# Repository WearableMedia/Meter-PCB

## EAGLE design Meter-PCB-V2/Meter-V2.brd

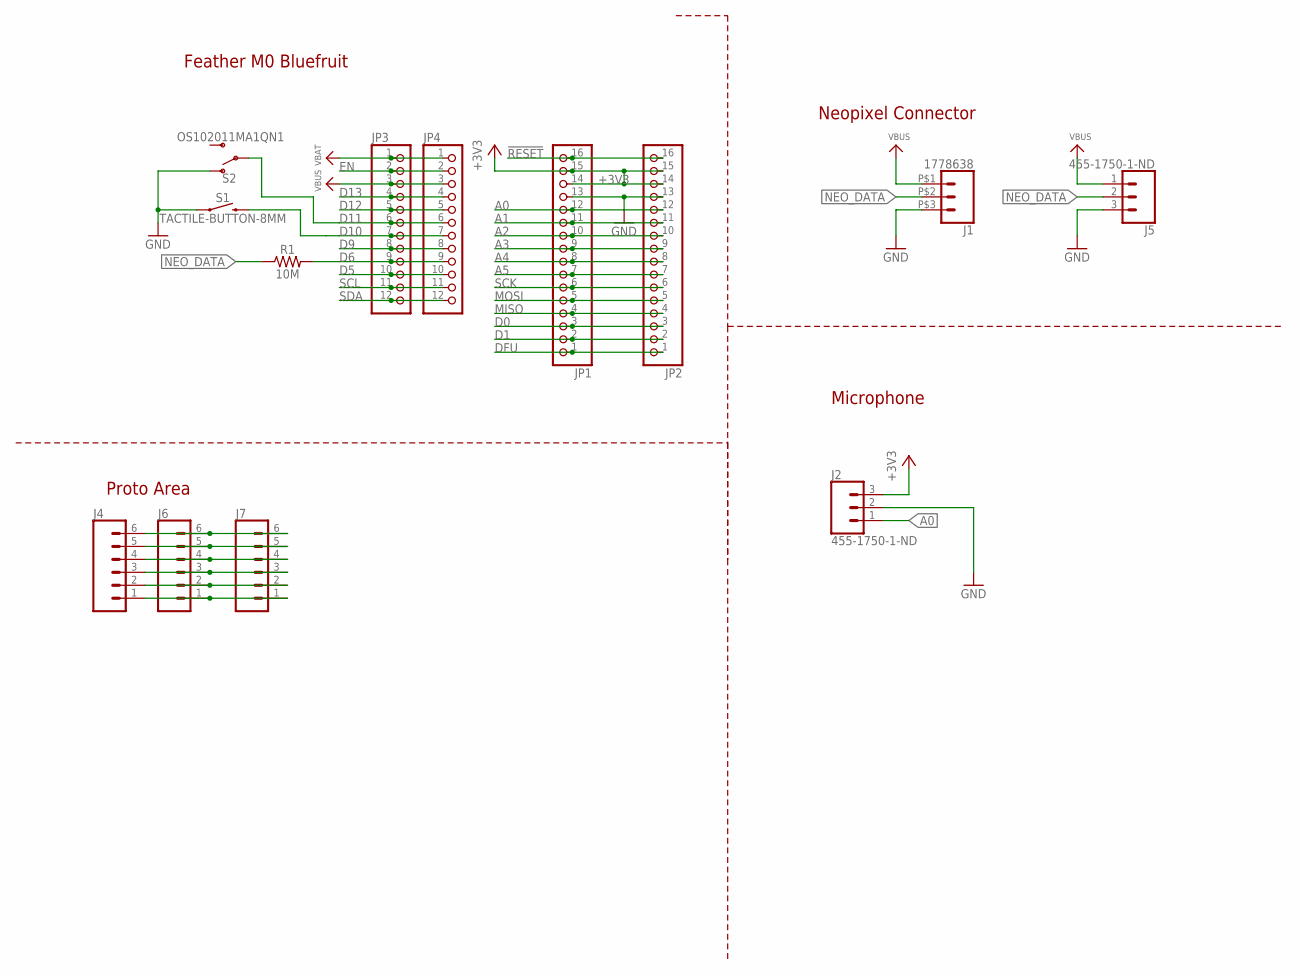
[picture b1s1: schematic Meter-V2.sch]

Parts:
J1: 1778638
J2, J5: 455-1750-1-ND; 1X03
J4, J6, J7: CONN_06NO_SILK_NO_POP; 1X06_NO_SILK
JP1, JP2: HEADER-1X16ROUND; 1X16_ROUND
JP3, JP4: HEADER-1X12; 1X12_ROUND
R1: 10M; AXIAL-0.3
S1: TACTILE-BUTTON-8MM; BUTTON-8MM
S2: OS102011MA1QN1

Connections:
!RESET: JP1.16, JP2.16
+3V3: J2.3, JP1.14, JP1.15, JP2.14, JP2.15
A0: J2.1, JP1.12, JP2.12
A1: JP1.11, JP2.11
A2: JP1.10, JP2.10
A3: JP1.9, JP2.9
A4: JP1.8, JP2.8
A5: JP1.7, JP2.7
D0: JP1.3, JP2.3
D1: JP1.2, JP2.2
D5: JP3.10, JP4.10
D6: JP3.9, JP4.9, R1.P$2 (2)
D9: JP3.8, JP4.8
D10: JP3.7, JP4.7, S1.P$2 (2), S1.P$3 (2)
D11: JP3.6, JP4.6, S2.P$2
D12: JP3.5, JP4.5
D13: JP3.4, JP4.4
DFU: JP1.1, JP2.1
EN: JP3.2, JP4.2
GND: J1.P$3 (3), J2.2, J5.3, JP1.13, JP2.13, S1.P$1 (1), S1.P$4 (1), S2.P$1 (O)
MISO: JP1.4, JP2.4
MOSI: JP1.5, JP2.5
unnamed: J4.6, J6.6, J7.6
unnamed: J4.5, J6.5, J7.5
unnamed: J4.4, J6.4, J7.4
unnamed: J4.3, J6.3, J7.3
unnamed: J4.2, J6.2, J7.2
unnamed: J4.1, J6.1, J7.1
NEO_DATA: J1.P$2 (2), J5.2, R1.P$1 (1)
SCK: JP1.6, JP2.6
SCL: JP3.11, JP4.11
SDA: JP3.12, JP4.12
VBAT: JP3.1, JP4.1
VBUS: J1.P$1 (1), J5.1, JP3.3, JP4.3

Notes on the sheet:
Feather M0 Bluefruit
Proto Area
Neopixel Connector
Microphone

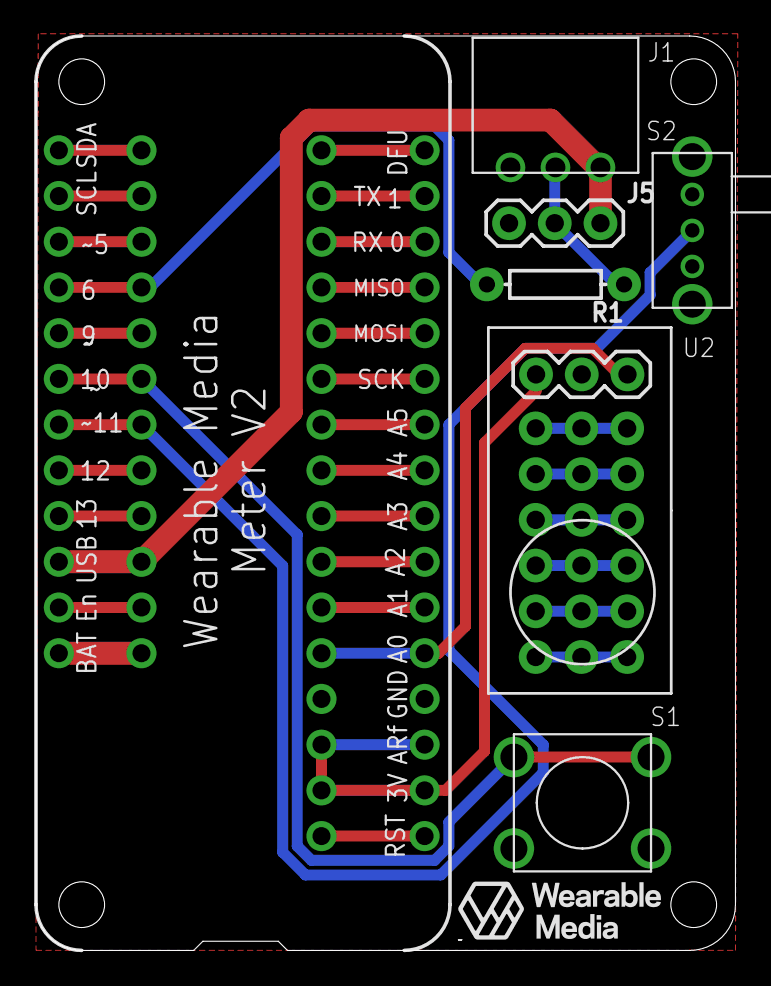
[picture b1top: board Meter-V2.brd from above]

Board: 2 copper layers, 38.9 x 50.8 mm, 15 parts (1 on the bottom side), 34 nets.

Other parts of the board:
U$3, U$4: WM_LOGO_MINI

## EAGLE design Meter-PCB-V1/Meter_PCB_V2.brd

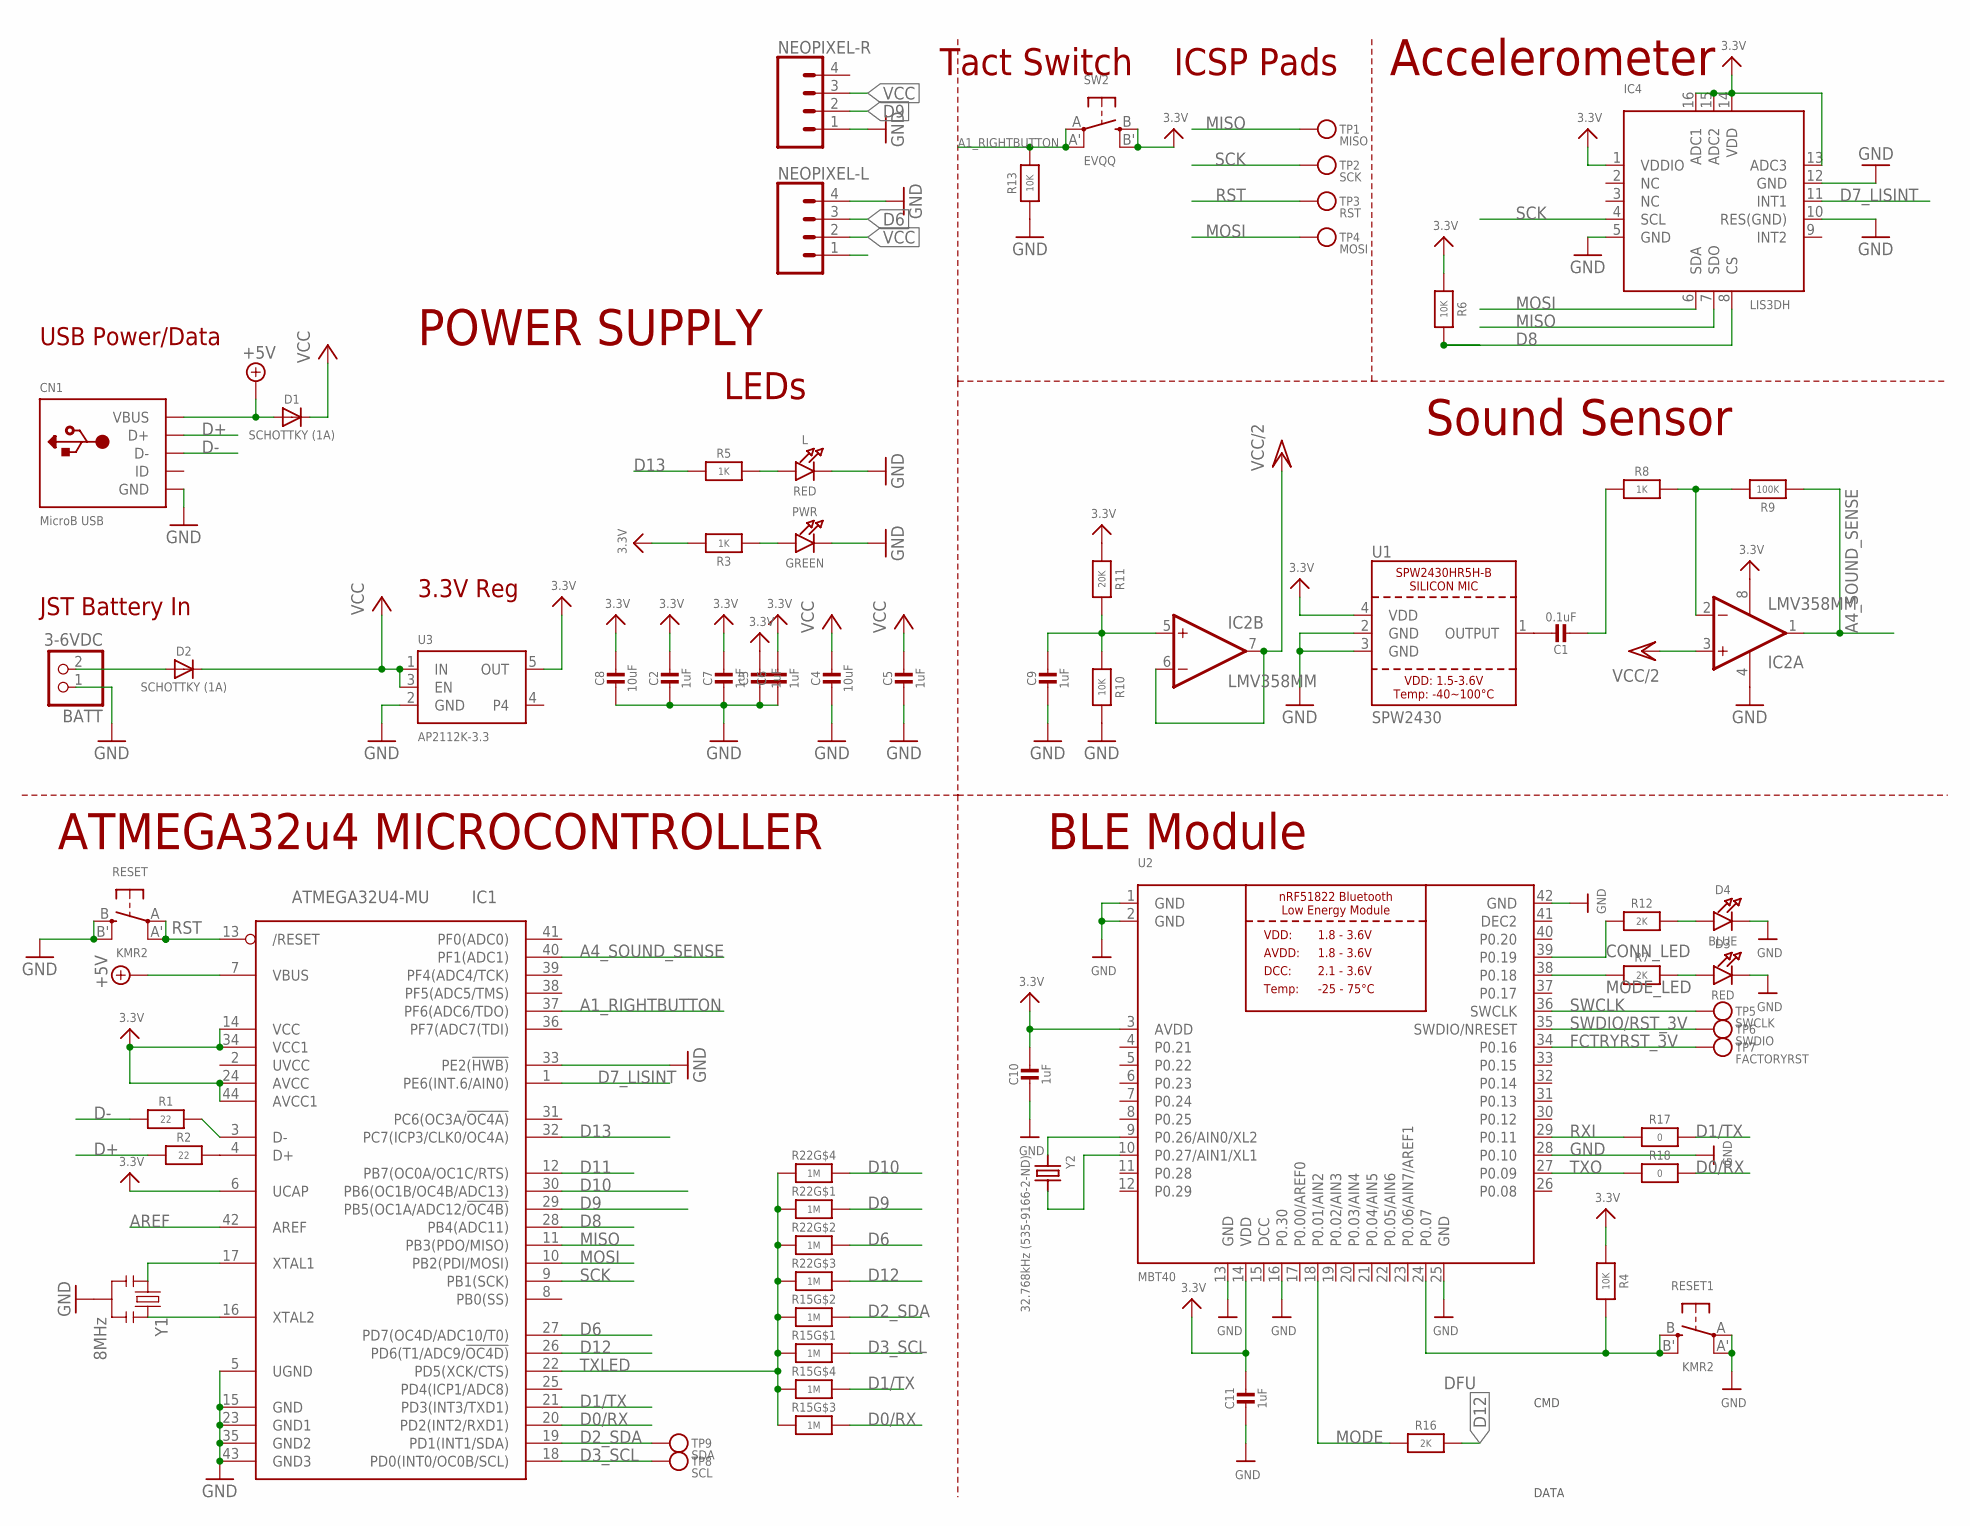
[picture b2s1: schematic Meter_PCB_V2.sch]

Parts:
BATT: 3-6VDC; JSTPH2
C1: 0.1uF; 0603-NO
C2, C3, C5, C6, C7, C9: 1uF; 0603-NO
C4, C8: 10uF; 0805-NO
C10, C11: 1uF; 0805-NO
CN1: MicroB USB; 4UCONN_20329_V2
D1, D2: SCHOTTKY (1A); SOD-123
D3: RED; CHIPLED_0805_NOOUTLINE
D4: BLUE; CHIPLED_0805_NOOUTLINE
IC1: ATMEGA32U4-MU; TQFN44_7MM
IC2: LMV358MM; MSOP08
IC4: LIS3DH; LGA16_3X3MM
L: RED; CHIPLED_0805_NOOUTLINE
NEOPIXEL-L: CONN_04; 1X04
NEOPIXEL-R: CONN_04; 1X04
PWR: GREEN; CHIPLED_0805_NOOUTLINE
R1, R2: 22; 0603-NO
R3, R5, R8: 1K; 0603-NO
R4: 10K; 0805-NO
R6, R10, R13: 10K; 0603-NO
R7, R12, R16: 2K; 0805-NO
R9: 100K; 0603-NO
R11: 20K; 0603-NO
R15, R22: 1M; RESPACK_4X0603_NO
R17, R18: 0; 0603-NO
RESET, RESET1: KMR2; BTN_KMR2_4.6X2.8
SW2: EVQQ; EVQ-Q2_SMALLER
TP1: MISO; TESTPOINT_ROUND_1.5MM
TP2: SCK; TESTPOINT_ROUND_1.5MM
TP3: RST; TESTPOINT_ROUND_1.5MM
TP4: MOSI; TESTPOINT_ROUND_1.5MM
TP5: SWCLK; TESTPOINT_ROUND_1.5MM
TP6: SWDIO; TESTPOINT_ROUND_1.5MM
TP7: FACTORYRST; TESTPOINT_ROUND_1.5MM
TP8: SCL; TESTPOINT_ROUND_1.5MM
TP9: SDA; TESTPOINT_ROUND_1.5MM
U1: SPW2430; SPW2430HR5H-B
U2: MBT40; BLE_MODULE_RAYTAC_MDBT40
U3: AP2112K-3.3; SOT23-5
Y1: 8MHz; RESONATOR-SMD
Y2: 32.768kHz (535-9166-2-ND); CRYSTAL_CYL_2X6MM_SMT

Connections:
3.3V: C2.1, C3.1, C6.1, C7.1, C8.1, C10.1, C11.1, IC1.6 (UCAP), IC1.14 (VCC), IC1.24 (AVCC), IC1.34 (VCC1), IC1.44 (AVCC1), IC2.8 (V+), IC4.1 (VDDIO), IC4.13 (ADC3), IC4.14 (VDD), IC4.15 (ADC2), IC4.16 (ADC1), NEOPIXEL-L.1, R3.2, R4.1, R6.1, R11.1, SW2.B (S), SW2.B' (S1), U1.4 (VDD), U2.3 (AVDD), U2.14 (VDD), U3.5 (OUT)
+5V: CN1.VBUS, D1.A, IC1.7 (VBUS)
A1_RIGHTBUTTON: IC1.37 (PF6(ADC6/TDO)), R13.2, SW2.A, SW2.A' (P1)
A4_SOUND_SENSE: IC1.40 (PF1(ADC1)), IC2.1 (OUT), R9.1
AREF: IC1.42 (AREF)
CONN_LED: R12.1, U2.39 (P0.19)
D0/RX: IC1.20 (PD2(INT2/RXD1)), R15.6 (2), R18.2
D1/TX: IC1.21 (PD3(INT3/TXD1)), R15.5 (2), R17.2
D2_SDA: IC1.19 (PD1(INT1/SDA)), R15.7 (2), TP9.P$1
D3_SCL: IC1.18 (PD0(INT0/OC0B/SCL)), R15.8 (2), TP8.P$1
D6: IC1.27 (PD7(OC4D/ADC10/T0)), NEOPIXEL-L.3, R22.7 (2)
D7_LISINT: IC1.1 (PE6(INT.6/AIN0)), IC4.11 (INT1)
D8: IC1.28 (PB4(ADC11)), IC4.8 (CS), R6.2
D9: IC1.29 (PB5(OC1A/ADC12/!OC4B)), NEOPIXEL-R.2, R22.8 (2)
D10: IC1.30 (PB6(OC1B/OC4B/ADC13)), R22.5 (2)
D11: IC1.12 (PB7(OC0A/OC1C/RTS))
D12: IC1.26 (PD6(T1/ADC9/!OC4D)), R16.2, R22.6 (2)
D13: IC1.32 (PC7(ICP3/CLK0/OC4A)), R5.1
D+: CN1.D+, R2.1
D-: CN1.D-, R1.1
DCC: U2.15 (DCC)
DEC2: U2.41 (DEC2)
DFU: R4.2, RESET1.B (S), RESET1.B' (S1), U2.24 (P0.07)
FCTRYRST_3V: TP7.P$1, U2.34 (P0.16)
GND: BATT.1, C2.2, C3.2, C4.2, C5.2, C6.2, C7.2, C8.2, C9.2, C10.2, C11.2, CN1.BASE@1 (GND), CN1.BASE@2 (GND), CN1.GND, CN1.SPRT@1 (GND), CN1.SPRT@2 (GND), CN1.SPRT@3 (GND), CN1.SPRT@4 (GND), D3.C, D4.C, IC1.5 (UGND), IC1.15 (GND), IC1.23 (GND1), IC1.33 (PE2(!HWB)), IC1.35 (GND2), IC1.43 (GND3), IC2.4 (V-), IC4.5 (GND), IC4.10 (RES(GND)), IC4.12 (GND), L.C, NEOPIXEL-L.4, NEOPIXEL-R.1, PWR.C, R10.2, R13.1, RESET.B (S), RESET.B' (S1), RESET1.A, RESET1.A' (P1), U1.2 (GND), U1.3 (GND), U2.1 (GND), U2.2 (GND), U2.13 (GND), U2.16 (P0.30), U2.25 (GND), U2.28 (P0.10), U2.42 (GND), U3.2 (GND), Y1.2
MISO: IC1.11 (PB3(PDO/MISO)), IC4.7 (SDO), TP1.P$1
MODE: R16.1, U2.18 (P0.01/AIN2)
MODE_LED: R7.1, U2.38 (P0.18)
MOSI: IC1.10 (PB2(PDI/MOSI)), IC4.6 (SDA), TP4.P$1
unnamed: PWR.A, R3.1
unnamed: IC2.2 (-IN), R8.2, R9.2
unnamed: IC1.3 (D-), R1.2
unnamed: IC1.4 (D+), R2.2
unnamed: D3.A, R7.2
unnamed: C9.1, IC2.5 (+IN), R10.1, R11.2
unnamed: BATT.2, D2.A
unnamed: IC1.17 (XTAL1), Y1.1
unnamed: IC1.16 (XTAL2), Y1.3
unnamed: L.A, R5.2
unnamed: D4.A, R12.2
unnamed: U2.9 (P0.26/AIN0/XL2), Y2.1
unnamed: U2.10 (P0.27/AIN1/XL1), Y2.2
unnamed: C1.2, R8.1
RST: IC1.13 (/RESET), RESET.A, RESET.A' (P1), TP3.P$1
RXI: R17.1, U2.29 (P0.11)
SCK: IC1.9 (PB1(SCK)), IC4.4 (SCL), TP2.P$1
SOUNDOUT: C1.1, U1.1 (OUTPUT)
SWCLK: TP5.P$1, U2.36 (SWCLK)
SWDIO/RST_3V: TP6.P$1, U2.35 (SWDIO/NRESET)
TXLED: IC1.22 (PD5(XCK/CTS)), R15.1, R15.2 (1), R15.3 (1), R15.4 (1), R22.1, R22.2 (1), R22.3 (1), R22.4 (1)
TXO: R18.1, U2.27 (P0.09)
VCC: C4.1, C5.1, D1.C, D2.C, NEOPIXEL-L.2, NEOPIXEL-R.3, U3.1 (IN), U3.3 (EN)
VCC/2: IC2.3 (+IN), IC2.6 (-IN), IC2.7 (OUT)

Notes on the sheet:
ATMEGA32u4 MICROCONTROLLER
USB Power/Data
JST Battery In
3.3V Reg
POWER SUPPLY
Sound Sensor
Tact Switch
LEDs
ICSP Pads
Accelerometer
DATA
CMD
BLE Module

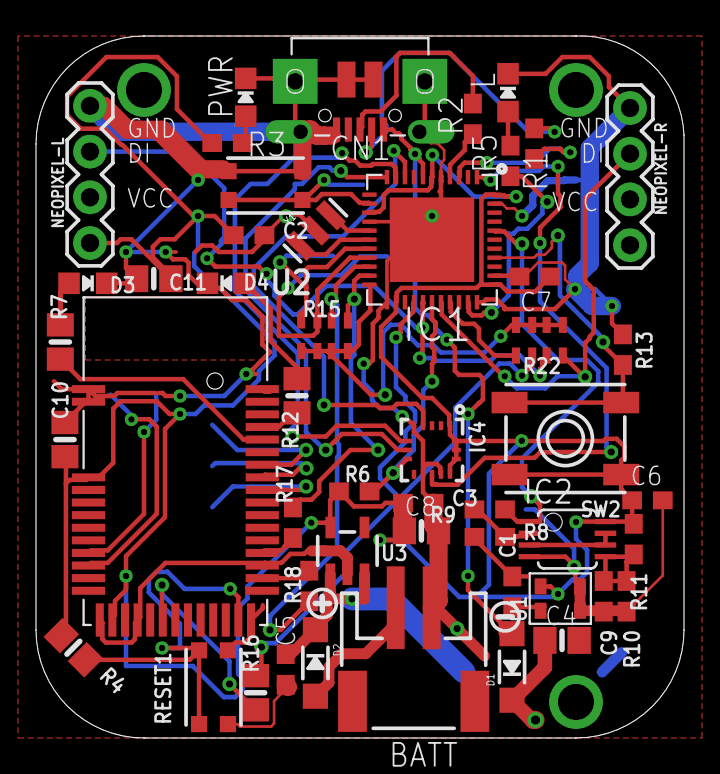
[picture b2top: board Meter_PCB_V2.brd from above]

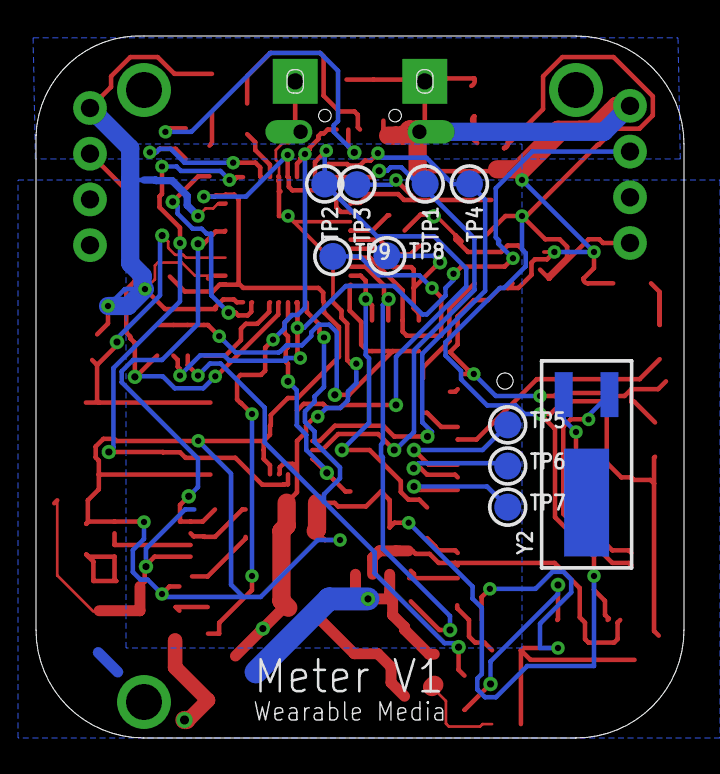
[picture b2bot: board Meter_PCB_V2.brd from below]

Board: 2 copper layers, 36.0 x 39.0 mm, 62 parts (11 on the bottom side), 49 nets.

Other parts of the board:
U$1: SYMBOL_MINUS
U$35: SYMBOL_PLUS
U$46: CPLAYBACK

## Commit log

2018-04-24 init
2018-04-30 finished board design
2018-05-19 finished brd

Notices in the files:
parts and their libraries:
microbuilder: This work is placed in the public domain, and may be freely used for commercial and non-commercial work with the following conditions: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
SparkFun: Licensing: CC v3.0 Share-Alike You are welcome to use this library for commercial purposes.
